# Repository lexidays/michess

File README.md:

# michess ♟️

An open-source NFC-based smart chess board powered by a Raspberry Pi. Place any piece on any square and the board knows exactly what it is and where it is - no setup routine, no special starting position required.

The board uses LEDs embedded behind a wood veneer to indicate the chess engine's moves, creating a clean physical interface for playing against a computer opponent.

---

## Features

- **Full piece identification** - NFC tags in each piece base, detected by a matrix of antennas under the board
- **Arbitrary position recognition** - pick up mid-game, set up a puzzle, analyse a position
- **LED move indicators** - subtle lighting behind the veneer shows the engine's chosen move
- **Stockfish integration** - plays via the standard UCI chess engine interface
- **Open design** - all hardware designs and software are freely available

---

## How It Works

64 NFC antennas sit beneath the board, one per square, managed by a hierarchical multiplexer system. A Raspberry Pi 4 scans the full board in under 2 seconds, determines the game state, passes it to Stockfish, and lights up the appropriate squares.

See [`docs/architecture/`](docs/architecture/) for full system diagrams.

---

## Repository Structure

```
michess/
├── hardware/               # Schematics, PCB layouts, BOM, antenna designs
├── firmware/               # Low-level microcontroller code (if applicable)
├── software/
│   ├── board_reader/       # NFC matrix scanning
│   ├── chess_engine/       # Stockfish/UCI integration
│   └── led_controller/     # LED matrix control
├── development/            # Throwaway hardware/learning test harnesses
├── docs/
│   └── architecture/       # System diagrams and design notes
└── tests/
```

---

## Hardware Requirements

| Component | Quantity | Notes |
|---|---|---|
| Raspberry Pi 4 | 1 | Main controller |
| PN532 NFC reader modules | 8 | One per 8-square group |
| CD74HC4067 16-channel multiplexers | 4 | For antenna switching |
| NFC tags (13.56 MHz) | 32 | Embedded in piece bases |
| Custom loop antennas | 64 | One per square, ~1–2 μH |
| WS2812B LEDs | 64+ | For move indication |

See [`hardware/bom/`](hardware/bom/) for a full bill of materials with UK suppliers and current pricing.

---

## Getting Started

### Software Setup

```bash
# Clone the repo
git clone https://github.com/lexidays/michess.git
cd michess

# Create a Python virtual environment
python3 -m venv venv
source venv/bin/activate

# Install dependencies
pip install -r requirements.txt

# Run
python software/main.py
```

### Hardware Setup

See [`docs/setup.md`](docs/setup.md) for full wiring instructions and assembly guide.

---

## Licences

This project uses different licences for different parts:

| Part | Licence |
|---|---|
| Software | [GPL-3.0](LICENSE) |
| Hardware designs | [CERN-OHL-S v2](hardware/LICENSE) |
| Documentation | [CC BY-SA 4.0](docs/LICENSE) |

In short: you are free to use, modify, and build on michess for any purpose - including building your own board - but you must share any changes under the same terms. Commercial use is permitted, but derived works cannot be closed source.

---

## Contributing

Contributions are very welcome - whether that's hardware improvements, software features, bug fixes, or documentation. Please open an issue first to discuss larger changes.

---

## Project Status

🚧 **Early development** - currently prototyping the NFC matrix on a 2×2 test board.

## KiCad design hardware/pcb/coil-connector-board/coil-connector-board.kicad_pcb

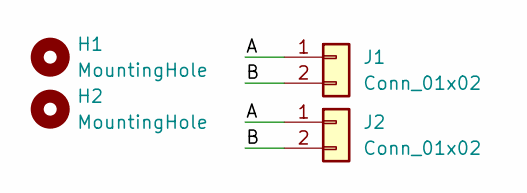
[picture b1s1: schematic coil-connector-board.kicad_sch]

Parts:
H1, H2: MountingHole; MountingHole_3.2mm_M3
J1: Conn_01x02; PinHeader_1x02_P2.54mm_Vertical
J2: Conn_01x02; JST_PH_S2B-PH-K_1x02_P2.00mm_Horizontal

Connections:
/A: J1.1, J2.1
/B: J1.2, J2.2

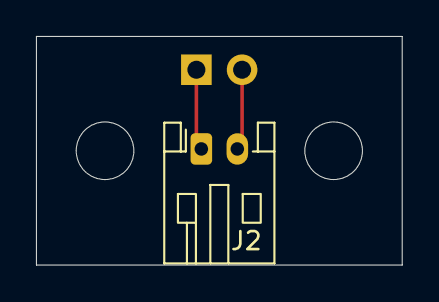
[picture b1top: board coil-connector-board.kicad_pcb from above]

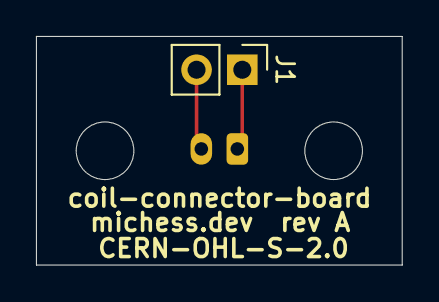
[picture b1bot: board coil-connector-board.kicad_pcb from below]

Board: 2 copper layers, 20.3 x 12.7 mm, 4 parts (3 on the bottom side), 2 nets.

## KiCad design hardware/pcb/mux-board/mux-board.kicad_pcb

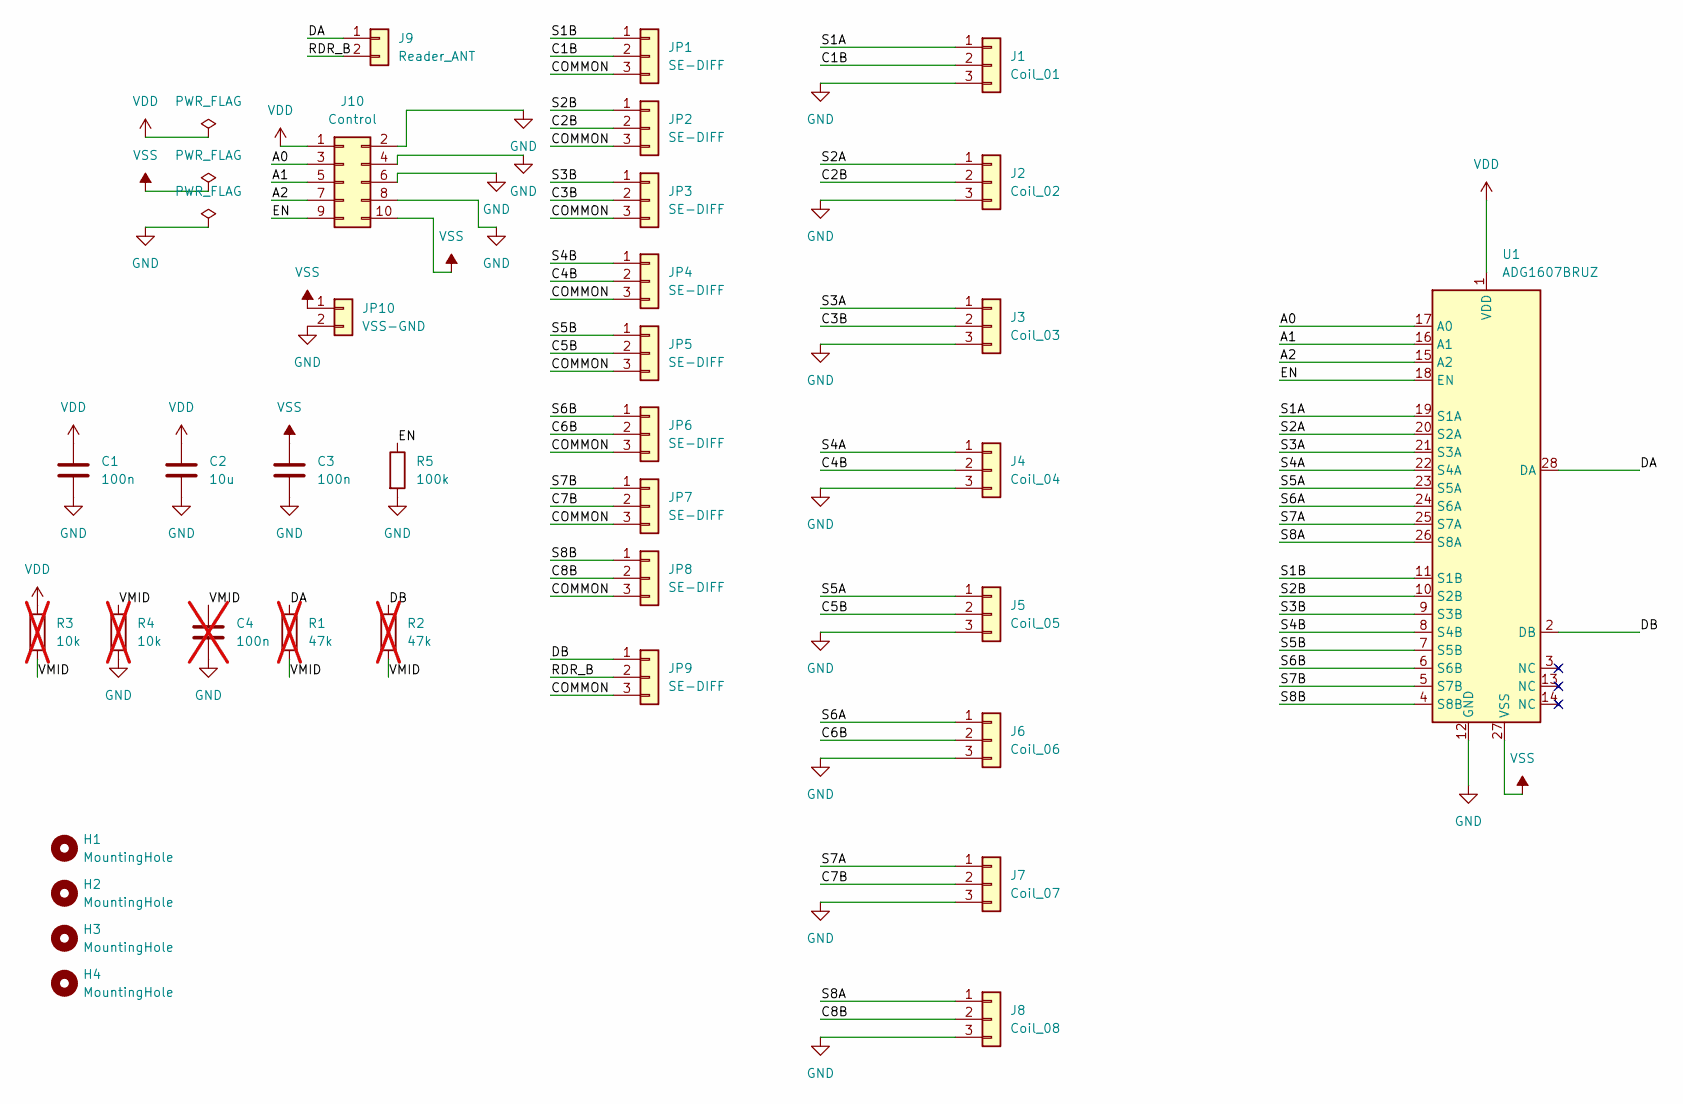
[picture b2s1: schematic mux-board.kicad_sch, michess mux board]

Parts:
C1, C3: 100n; C_0805_2012Metric_Pad1.18x1.45mm_HandSolder
C2: 10u; C_0805_2012Metric_Pad1.18x1.45mm_HandSolder
C4: 100n; C_0805_2012Metric_Pad1.18x1.45mm_HandSolder; not fitted
H1, H2, H3, H4: MountingHole; MountingHole_3.2mm_M3
J1: Coil_01; JST_PH_S3B-PH-K_1x03_P2.00mm_Horizontal
J2: Coil_02; JST_PH_S3B-PH-K_1x03_P2.00mm_Horizontal
J3: Coil_03; JST_PH_S3B-PH-K_1x03_P2.00mm_Horizontal
J4: Coil_04; JST_PH_S3B-PH-K_1x03_P2.00mm_Horizontal
J5: Coil_05; JST_PH_S3B-PH-K_1x03_P2.00mm_Horizontal
J6: Coil_06; JST_PH_S3B-PH-K_1x03_P2.00mm_Horizontal
J7: Coil_07; JST_PH_S3B-PH-K_1x03_P2.00mm_Horizontal
J8: Coil_08; JST_PH_S3B-PH-K_1x03_P2.00mm_Horizontal
J9: Reader_ANT; PinHeader_1x02_P2.54mm_Vertical
J10: Control; IDC-Header_2x05_P2.54mm_Horizontal
JP1, JP2, JP3, JP4, JP5, JP6, JP7, JP8, JP9: SE-DIFF; PinHeader_1x03_P2.54mm_Vertical
JP10: VSS-GND; PinHeader_1x02_P2.54mm_Vertical
R1, R2: 47k; R_Axial_DIN0309_L9.0mm_D3.2mm_P12.70mm_Horizontal; not fitted
R3, R4: 10k; R_Axial_DIN0309_L9.0mm_D3.2mm_P12.70mm_Horizontal; not fitted
R5: 100k; R_Axial_DIN0309_L9.0mm_D3.2mm_P12.70mm_Horizontal
U1: ADG1607BRUZ; TSSOP-28_4.4x9.7mm_P0.65mm

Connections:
/A0: J10.3, U1.17 (A0)
/A1: J10.5, U1.16 (A1)
/A2: J10.7, U1.15 (A2)
/C1B: J1.2, JP1.2
/C2B: J2.2, JP2.2
/C3B: J3.2, JP3.2
/C4B: J4.2, JP4.2
/C5B: J5.2, JP5.2
/C6B: J6.2, JP6.2
/C7B: J7.2, JP7.2
/C8B: J8.2, JP8.2
/COMMON: JP1.3, JP2.3, JP3.3, JP4.3, JP5.3, JP6.3, JP7.3, JP8.3, JP9.3
/DA: J9.1, R1.1, U1.28 (DA)
/DB: JP9.1, R2.1, U1.2 (DB)
/EN: J10.9, R5.1, U1.18 (EN)
/RDR_B: J9.2, JP9.2
/S1A: J1.1, U1.19 (S1A)
/S1B: JP1.1, U1.11 (S1B)
/S2A: J2.1, U1.20 (S2A)
/S2B: JP2.1, U1.10 (S2B)
/S3A: J3.1, U1.21 (S3A)
/S3B: JP3.1, U1.9 (S3B)
/S4A: J4.1, U1.22 (S4A)
/S4B: JP4.1, U1.8 (S4B)
/S5A: J5.1, U1.23 (S5A)
/S5B: JP5.1, U1.7 (S5B)
/S6A: J6.1, U1.24 (S6A)
/S6B: JP6.1, U1.6 (S6B)
/S7A: J7.1, U1.25 (S7A)
/S7B: JP7.1, U1.5 (S7B)
/S8A: J8.1, U1.26 (S8A)
/S8B: JP8.1, U1.4 (S8B)
/VMID: C4.1, R1.2, R2.2, R3.2, R4.1
GND: C1.2, C2.2, C3.2, C4.2, J1.3, J2.3, J3.3, J4.3, J5.3, J6.3, J7.3, J8.3, J10.2, J10.4, J10.6, J10.8, JP10.2, R4.2, R5.2, U1.12 (GND)
VDD: C1.1, C2.1, J10.1, R3.1, U1.1 (VDD)
VSS: C3.1, J10.10, JP10.1, U1.27 (VSS)

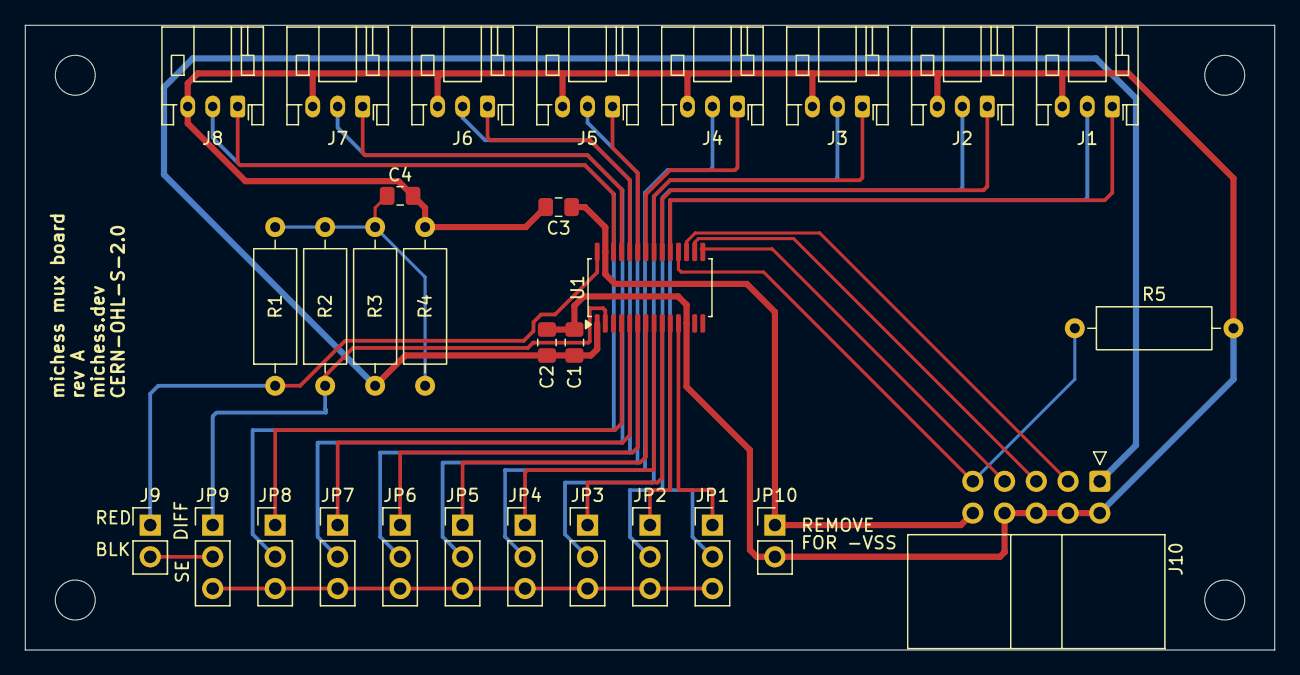
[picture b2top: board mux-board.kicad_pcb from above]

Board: 2 copper layers, 100.0 x 50.0 mm, 34 parts (0 on the bottom side), 36 nets.

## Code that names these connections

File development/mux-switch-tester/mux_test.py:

"""
michess bring-up step 3: prove the ADG1607 switches.

No RF here. The Pi drives the address lines (A0-A2) and EN, and you
measure each channel with the multimeter on the ohms range. Your
readings are saved to a CSV so every channel has a number on record.

Wiring (breakout pin -> Pi):
  1  VDD -> 3.3 V        12 GND -> GND        27 VSS -> GND
  17 A0  -> GPIO17       16 A1  -> GPIO27     15 A2  -> GPIO22
  18 EN  -> GPIO23       (3, 13, 14 not connected)

Pinout used for the prompts:
  DA = 28, DB = 2
  S1A..S8A = pins 19..26
  S1B..S8B = pins 11..4
"""

import csv
from datetime import datetime

from gpiozero import DigitalOutputDevice

A0 = DigitalOutputDevice(17)
A1 = DigitalOutputDevice(27)
A2 = DigitalOutputDevice(22)
EN = DigitalOutputDevice(23)


def select(channel: int) -> None:
    """Channel 1-8 -> 3-bit address (channel 1 = 000, channel 8 = 111)."""
    code = channel - 1
    A0.value = code & 1
    A1.value = (code >> 1) & 1
    A2.value = (code >> 2) & 1


def a_pin(channel: int) -> int:
    return 18 + channel  # S1A = 19 ... S8A = 26


def b_pin(channel: int) -> int:
    return 12 - channel  # S1B = 11 ... S8B = 4


def ask(prompt: str) -> str:
    return input(prompt).strip() or "-"


def main() -> None:
    rows = []
    EN.off()

    print("\n=== Lead check ===")
    lead = ask("Touch the probes together. Ohms shown (lead resistance): ")
    rows.append(["leads", "", "probes shorted", lead])

    print("\n=== EN LOW: everything should be off ===")
    select(1)
    r = ask("Ohms from pin 19 (S1A) to pin 28 (DA), expect OL: ")
    rows.append(["EN low", "000", "19-28", r])

    for ch in range(1, 9):
        select(ch)
        EN.on()
        code = format(ch - 1, "03b")
        other = ch % 8 + 1  # the next channel round, should be off

        print(f"\n=== Channel {ch} selected (A2 A1 A0 = {code}), EN HIGH ===")
        ra = ask(f"  Pin {a_pin(ch)} (S{ch}A) to pin 28 (DA), expect low ohms: ")
        rb = ask(f"  Pin {b_pin(ch)} (S{ch}B) to pin 2 (DB),  expect low ohms: ")
        ro = ask(f"  Pin {a_pin(other)} (S{other}A) to pin 28 (DA), expect OL:  ")

        rows.append([f"ch{ch} on", code, f"{a_pin(ch)}-28", ra])
        rows.append([f"ch{ch} on", code, f"{b_pin(ch)}-2", rb])
        rows.append([f"ch{ch} on, ch{other} should be off", code,
                     f"{a_pin(other)}-28", ro])

    EN.off()
    print("\n=== EN LOW again ===")
    r = ask("Ohms from pin 26 (S8A) to pin 28 (DA), expect OL: ")
    rows.append(["EN low (after)", "111", "26-28", r])

    filename = f"mux_results_{datetime.now():%Y%m%d_%H%M}.csv"
    with open(filename, "w", newline="") as f:
        writer = csv.writer(f)
        writer.writerow(["state", "A2A1A0", "pins", "reading"])
        writer.writerows(rows)
    print(f"\nSaved to {filename}")


if __name__ == "__main__":
    try:
        main()
    finally:
        EN.off()  # always leave every switch off

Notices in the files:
hardware/pcb/coil-connector-board/coil-connector-board.kicad_pcb:
CERN-OHL-S-2.0
hardware/pcb/mux-board/mux-board.kicad_sch:
Licence: CERN-OHL-S v2
